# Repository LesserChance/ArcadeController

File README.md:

# ArcadeController
The goal of this project is to make an easily-swappable control panel for a homebuilt arcade. There are two PCBs that are designed to mate through a ribbon cable connection. By default, this setup will allow for any control panel to have a maximum of 2 joysticks and 14 buttons (22 total digital inputs), 6 axes (e.g. 6 spinners) and two USB devices. You can easily edit the program on the arduino to assure all of your control panels will work, though, for instance if you need more digital inputs and fewer axes.

As I build out more control panels I'll be adding pictures and diagrams of how everything operates.

## Electronics
### PCB: Panel
One Panel PCB exists for each control panel. The Panel PCB exists as the interface between the controls (joysticks, trackballs, spinners, USB devices) and the Main interface. It is split into various sections. Full wiring diagrams can be found in the docs directory.

**Player One** Connected to "Player One" Micro.  
*Up, Down, Left, Right, B0-5*: Four directional wires, 6 button wires. (note that B6, B7 are not wired to anything)  
*X1, X2, Y1, Y2, Z1, Z2*: These utilize interrupt pins on the arduinos, and are used for encoder connections (trackball, spinner)  

**Player Two** Connected to "Player Two" Micro.  
*Up, Down, Left, Right, B0-5*: Four directional wires, 6 button wires. (note that B6, B7 are not wired to anything)  
*X1, X2, Y1, Y2, Z1, Z2*: These utilize interrupt pins on the arduinos, and are used for encoder connections (trackball, spinner)  

**+5v/Ground** Pulls +5v and Ground from "Player One" Micro. Useful for LEDs/etc

**USB** These directly wire to USB connection on the main control panel. These can be used to directly connect USB devices to your computer. Unfortunately these dont seem to be working just yet!

**DIP switch** Used to identify which control panel this is. Allows for different programming on the arduinos per control panel.  

For detailed wiring information see [the pinmap](docs/pinmap.md).

### PCB: Main

The Main PCB is what connects to your computer through USB. In total it requires four open USB ports. Only One Main PCB is necessary. The main panels houses two Arduino Micros.

**Micro Headers** These are the positions where you plug in Arduino Micros.

**Screw in Terminals** These can be used for shared functions e.g. Player 1/2 Start/Coin as well as menu or function buttons. 6 are connected to "Player One" Micro, and another 6 are connected to "Player Two" Micro.

### Arduino

The program is built to run on an [Ardunio Micro](https://store.arduino.cc/usa/arduino-micro). Two Arduino Micros are required for two-player functionality. Player One and the two additional USB devices will work fine with just one, though, if you can get away with a maximum of 17 total digital inputs on any control panel.

When plugged in the Arduinos will be treated as a joystick/mouse/keyboard by the computer based on the code used for the control panel. The joystick, by default is 2 axis (X/Y) and 12 button.

---

Schematics were designed in [Kicad](https://kicad-pcb.org/). I print PCBS with [JLCPCB](jlcpcb.com/).

# Documents
### [Pinmap](docs/pinmap.md)
The pinmap outlines how connections are bridged between the PCBs and how they function by default through USB. Panel->Main->Arduino->Function

### [Wiring](docs/wiring.md)
The wiring doc outlines standard wiring for trackballs and spinners directly into the Panel PCB.

# Supplies
_Prices are USD, do not include shipping, and are as of July 2020._

Buy extra screw-in terminals to make more control panels, and buy the Panel PCBs in bulk. Given the below prices you could create 10 easily-swappable control panels for ~$80, and you may be able to find those screw terminals more cheaply, or decide to bypass those, just solder in your connections and have it all for ~$40. Of course the price of buttons/joysticks/trackballs/steering wheels/etc is additional.

| Component | Part | Supply | Cost | Count |
|----------|----------|----------|----------|----------|
| Main | Arduino Micro | [Ardunio Store](https://store.arduino.cc/usa/arduino-micro-without-headers) | $12.30 | 2 |
| Main | PCB | [JLCPCB](jlcpcb.com/) | $7.00 | 1 (price is per 5 though - _minimum order_) |
| Main | Micro USB | [Digikey](https://www.digikey.com/product-detail/en/molex/0475890001/WM17143CT-ND/1832255) | $.87 | 2 |
| Main | Micro Pin Headers | [Digikey](https://www.digikey.com/product-detail/en/sullins-connector-solutions/PREC040SAAN-RC/S1012EC-40-ND/2774814) | $.51 | 2 |
| Main | Micro connection headers | [Digikey](https://www.digikey.com/product-detail/en/adafruit-industries-llc/598/1528-2537-ND/8299908) | $2.95 | 1 (cut each down to 17 pins) |
| Main | LEDs | Im sure you have some laying around | - | 3 |
| Main | Cable Header | [Digikey](https://www.digikey.com/product-detail/en/assmann-wsw-components/AWH-50G-E232-IDC/AE11157-ND/5050380) | $4.56 | 1 |
| Panel | PCB | [JLCPCB](jlcpcb.com/) | $12.00 | 1 (price was for 10) |
| Panel | USB Header | [Digikey](https://www.digikey.com/product-detail/en/assmann-wsw-components/AU-Y1008-2/AE11131-ND/5147142) | $1.07 | 1 |
| Panel | Ribbon Cable | [Digikey](https://www.digikey.com/product-detail/en/assmann-wsw-components/H3AAH-5018G/H3AAH-5018G-ND/1218717) | $3.27 | 1 |
| Panel | Cable Header | [Digikey](https://www.digikey.com/product-detail/en/sullins-connector-solutions/SBH11-PBPC-D25-ST-BK/S9176-ND/1990069) | $1.02 | 1 |
| Panel | DIP Switch | [Digikey](https://www.digikey.com/product-detail/en/cts-electrocomponents/208-4/CT2084-ND/20783) | $.69 | 1 |
| Main+Panel | Resistors | (3) 10k, 3 (220) | - | 6 |
| Main+Panel | Screw-in Terminal | [Digikey](https://www.digikey.com/products/en?keywords=TB001-500-12BE%20) | $1.73 | 5 (+4 for each additional panel) |

_Why do the PCBs have the Slurm logo on them? I dont know, I just really like Futurama and happened to have this image handy..._

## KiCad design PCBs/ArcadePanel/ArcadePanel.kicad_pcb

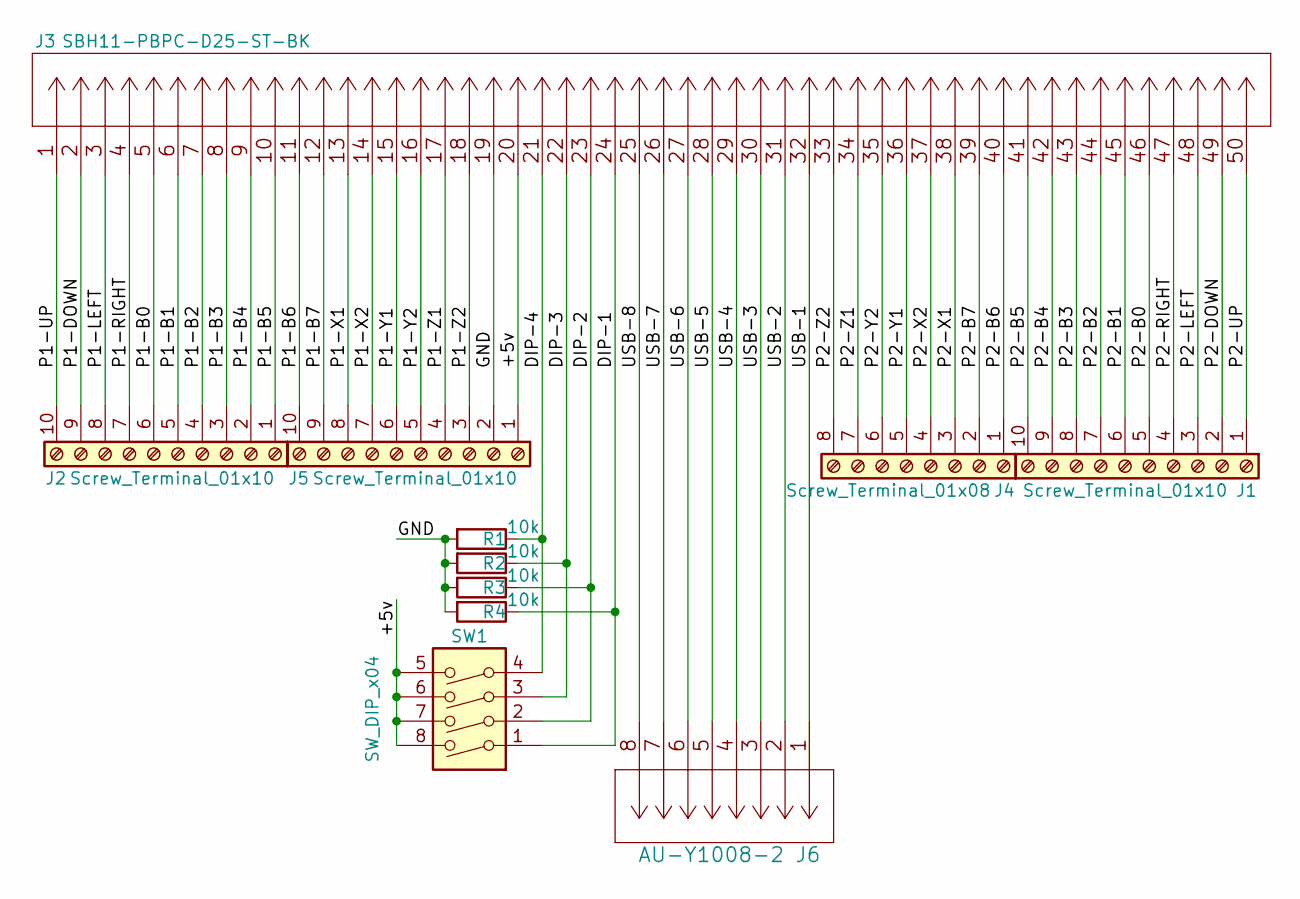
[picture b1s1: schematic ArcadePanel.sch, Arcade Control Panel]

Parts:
J1, J2, J5: Screw_Terminal_01x10; CUI_TB001-500-10BE
J3: SBH11-PBPC-D25-ST-BK
J4: Screw_Terminal_01x08; CUI_TB001-500-08BE
J6: AU-Y1008-2
R1, R2, R3, R4: 10k; R_Axial_DIN0204_L3.6mm_D1.6mm_P7.62mm_Horizontal
SW1: SW_DIP_x04; DIP-8_W7.62mm

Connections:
/+5v: J3.20, J5.1, SW1.5, SW1.6, SW1.7, SW1.8
/GND: J3.19, J5.2, R1.2, R2.2, R3.2, R4.2
/P1-B0: J2.6, J3.5
/P1-B1: J2.5, J3.6
/P1-B2: J2.4, J3.7
/P1-B3: J2.3, J3.8
/P1-B4: J2.2, J3.9
/P1-B5: J2.1, J3.10
/P1-B6: J3.11, J5.10
/P1-B7: J3.12, J5.9
/P1-DOWN: J2.9, J3.2
/P1-LEFT: J2.8, J3.3
/P1-RIGHT: J2.7, J3.4
/P1-UP: J2.10, J3.1
/P1-X1: J3.13, J5.8
/P1-X2: J3.14, J5.7
/P1-Y1: J3.15, J5.6
/P1-Y2: J3.16, J5.5
/P1-Z1: J3.17, J5.4
/P1-Z2: J3.18, J5.3
/P2-B0: J1.5, J3.46
/P2-B1: J1.6, J3.45
/P2-B2: J1.7, J3.44
/P2-B3: J1.8, J3.43
/P2-B4: J1.9, J3.42
/P2-B5: J1.10, J3.41
/P2-B6: J3.40, J4.1
/P2-B7: J3.39, J4.2
/P2-DOWN: J1.2, J3.49
/P2-LEFT: J1.3, J3.48
/P2-RIGHT: J1.4, J3.47
/P2-UP: J1.1, J3.50
/P2-X1: J3.38, J4.3
/P2-X2: J3.37, J4.4
/P2-Y1: J3.36, J4.5
/P2-Y2: J3.35, J4.6
/P2-Z1: J3.34, J4.7
/P2-Z2: J3.33, J4.8
unnamed: J3.21, R1.1, SW1.4
unnamed: J3.22, R2.1, SW1.3
unnamed: J3.23, R3.1, SW1.2
unnamed: J3.24, R4.1, SW1.1
unnamed: J3.25, J6.8
unnamed: J3.26, J6.7
unnamed: J3.27, J6.6
unnamed: J3.28, J6.5
unnamed: J3.29, J6.4
unnamed: J3.30, J6.3
unnamed: J3.31, J6.2
unnamed: J3.32, J6.1

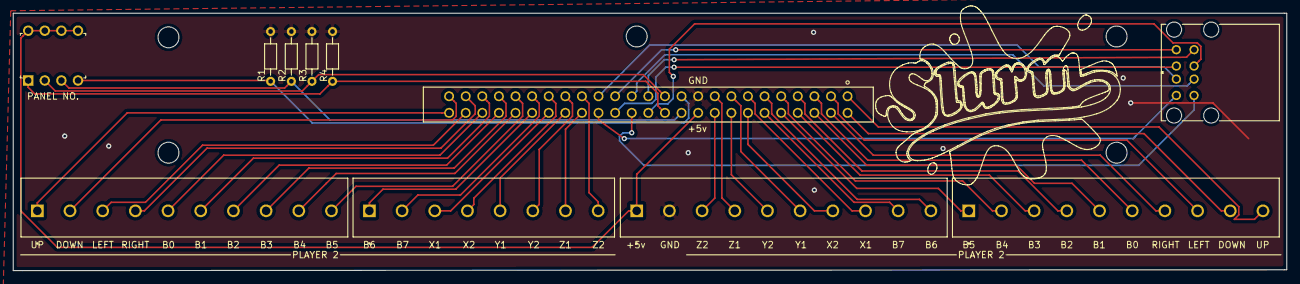
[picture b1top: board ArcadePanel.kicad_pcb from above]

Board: 2 copper layers, 194.8 x 39.4 mm, 16 parts (0 on the bottom side), 50 nets.

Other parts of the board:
4, 4#2, 4#3, 4#4, 4#5: MountingHole_3.2mm_M3

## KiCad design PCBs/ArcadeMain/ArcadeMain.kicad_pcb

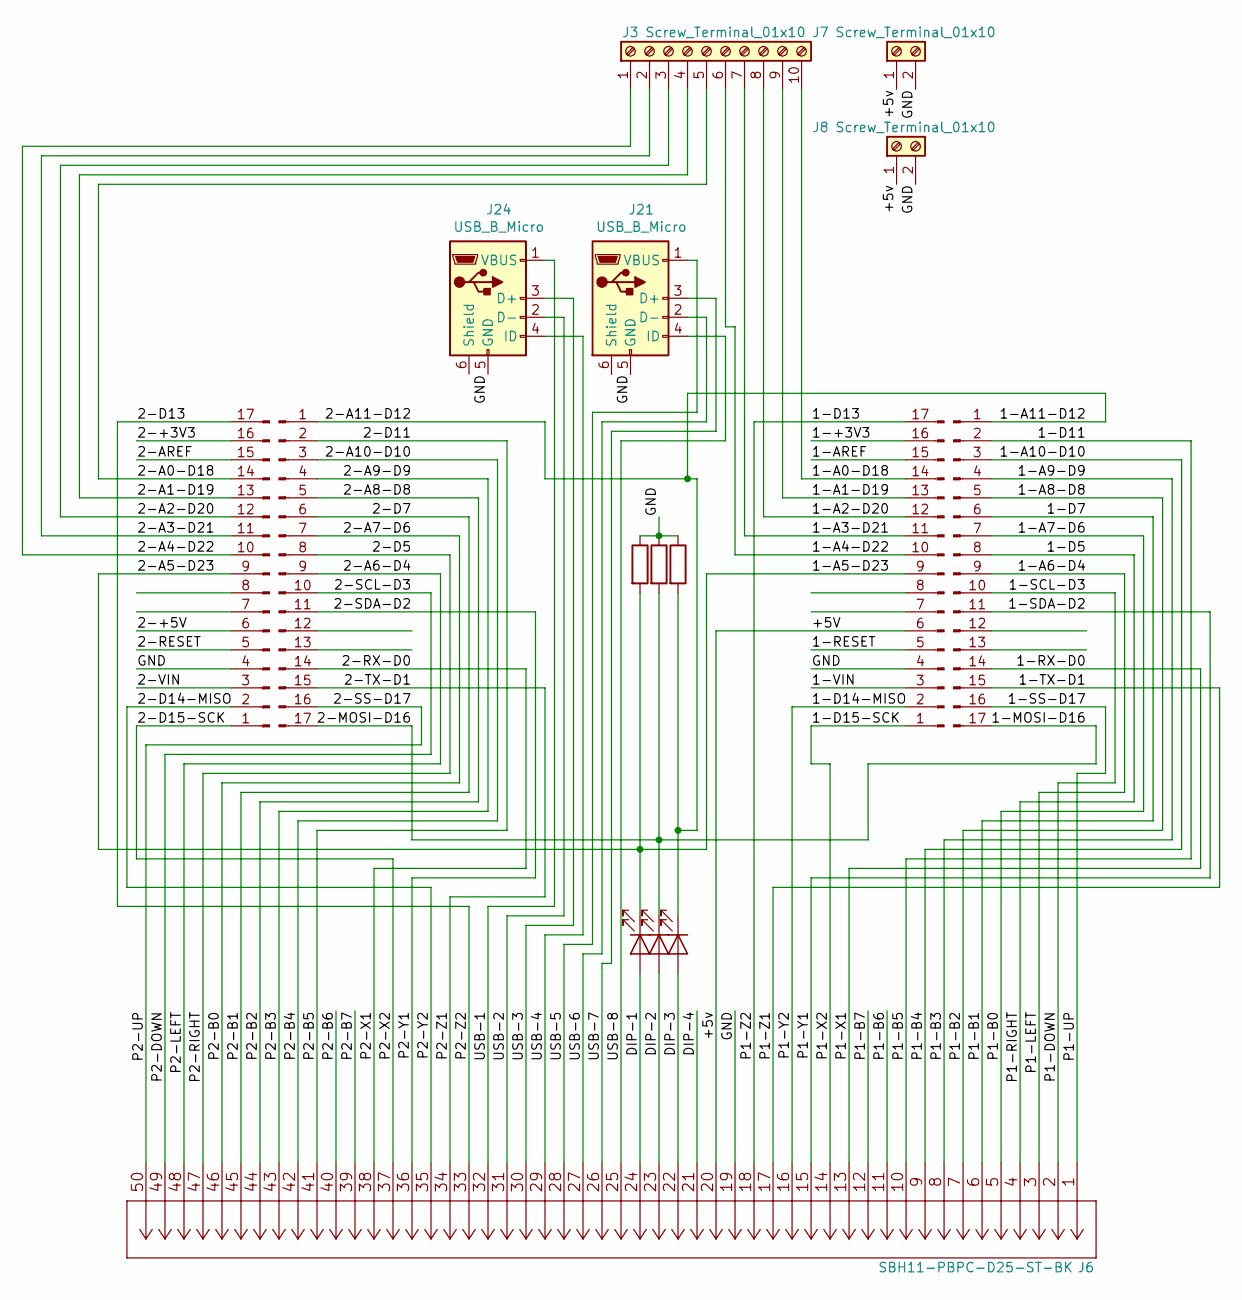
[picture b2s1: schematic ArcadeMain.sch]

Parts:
D1, D2, D3: LED; LED_D3.0mm
J1, J2, J4, J5: Conn_01x17_Male; PinHeader_1x17_P2.54mm_Vertical
J3: Screw_Terminal_01x10; CUI_TB001-500-10BE
J6: SBH11-PBPC-D25-ST-BK
J7, J8: Screw_Terminal_01x10; CUI_TB001-500-02BE
J21, J24: USB_B_Micro; GCT_USB3131-XX-0230-X_REVB
R1, R2, R3: 220; R_Axial_DIN0204_L3.6mm_D1.6mm_P7.62mm_Horizontal

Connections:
/1-+3V3: J1.16
/1-A0-D18: J1.14, J3.10
/1-A1-D19: J1.13, J3.9
/1-A2-D20: J1.12, J3.8
/1-A3-D21: J1.11, J3.7
/1-A4-D22: J1.10, J3.6
/1-A5-D23: D1.1 (K), J1.9, J4.9, R1.2
/1-A6-D4: J2.9, J6.3
/1-A7-D6: J2.7, J6.5
/1-A8-D8: J2.5, J6.7
/1-A9-D9: J2.4, J6.8
/1-A10-D10: J2.3, J6.9
/1-A11-D12: D3.1 (K), J2.1, J5.1, R3.2
/1-AREF: J1.15
/1-D5: J2.8, J6.4
/1-D7: J2.6, J6.6
/1-D11: J2.2, J6.10
/1-D13: J1.17, J6.18
/1-D14-MISO: J1.2, J6.16
/1-D15-SCK: J1.1, J6.14
/1-MOSI-D16: D2.1 (K), J2.17, J5.17, R2.2
/1-RESET: J1.5
/1-RX-D0: J2.14, J6.13
/1-SCL-D3: J2.10, J6.2
/1-SDA-D2: J2.11, J6.15
/1-SS-D17: J2.16, J6.1
/1-TX-D1: J2.15, J6.17
/1-VIN: J1.3
/2-+3V3: J4.16
/2-+5V: J4.6
/2-A0-D18: J3.5, J4.14
/2-A1-D19: J3.4, J4.13
/2-A2-D20: J3.3, J4.12
/2-A3-D21: J3.2, J4.11
/2-A4-D22: J3.1, J4.10
/2-A6-D4: J5.9, J6.48
/2-A7-D6: J5.7, J6.46
/2-A8-D8: J5.5, J6.44
/2-A9-D9: J5.4, J6.43
/2-A10-D10: J5.3, J6.42
/2-AREF: J4.15
/2-D5: J5.8, J6.47
/2-D7: J5.6, J6.45
/2-D11: J5.2, J6.41
/2-D13: J4.17, J6.33
/2-D14-MISO: J4.2, J6.35
/2-D15-SCK: J4.1, J6.37
/2-RESET: J4.5
/2-RX-D0: J5.14, J6.38
/2-SCL-D3: J5.10, J6.49
/2-SDA-D2: J5.11, J6.36
/2-SS-D17: J5.16, J6.50
/2-TX-D1: J5.15, J6.34
/2-VIN: J4.3
/+5V: J1.6, J6.20, J7.1, J8.1
/DIP-1: D1.2 (A), J6.24
/DIP-2: D2.2 (A), J6.23
/DIP-3: D3.2 (A), J6.22
/DIP-4: J6.21
/GND: J1.4, J4.4, J6.19, J7.2, J8.2, J21.5 (GND), J24.5 (GND), R1.1, R2.1, R3.1
/P1-B6: J6.11
/P1-B7: J6.12
/P2-B6: J6.40
/P2-B7: J6.39
/USB-1: J6.32, J24.1 (VBUS)
/USB-2: J6.31, J24.2 (D-)
/USB-3: J6.30, J24.3 (D+)
/USB-4: J6.29, J24.4 (ID)
/USB-5: J6.28, J21.1 (VBUS)
/USB-6: J6.27, J21.2 (D-)
/USB-7: J6.26, J21.3 (D+)
/USB-8: J6.25, J21.4 (ID)

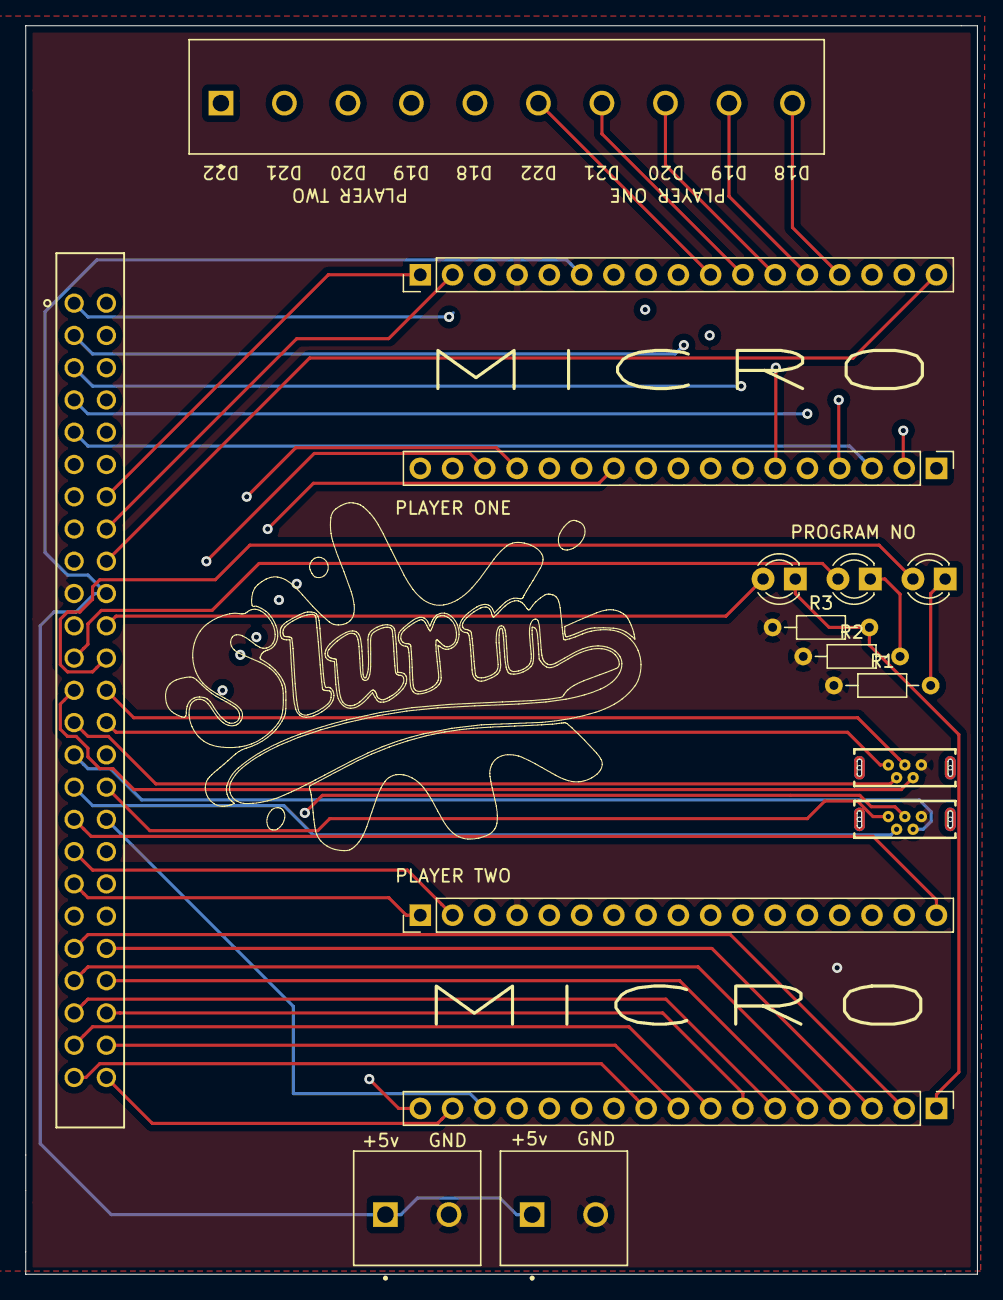
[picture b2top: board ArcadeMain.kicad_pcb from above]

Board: 4 copper layers, 74.9 x 98.3 mm, 16 parts (0 on the bottom side), 58 nets.

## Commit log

2020-07-11 Initial Docs
2020-07-11 Add Schematic PDFs
2020-07-19 v2 PCB revisions: switch to ribbon cable rather than PCB edge, add DIP switch for panel identifications
2020-07-26 Update skecth to use mouse and keyboard.
    Retroarch only allows a single controller to control the menu functions so mapping the main panel to keyboard keys gets around this. Additionally using joystick axes was not working for trackball inp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
2020-07-29 Panel 0 updates
    Panel 0 is now set up to use a 4 to 8 way servo controlled restrictor plate as well as button leds. controls are parses with the standard mame controls.xml file. Additionally split out the arduino co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
2020-07-29 add onend script to reset to default state
2020-07-30 Button LED fixes
    Some quick fixes after actually hooking everything up and trying it out
2020-07-31 Move serial functionality up
    even if a panel doesnt need to read it, it shouldnt fail to listen
2020-08-31 update utility scripts
    sendcontrol now reads directly from the attrat mode gamelist for quick lookup
2020-08-31 Add new panels to arudino logic
2020-08-31 Update Schematic references

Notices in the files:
parts and their libraries:
Copyright 2016 Accelerated Designs. All rights reserved.
